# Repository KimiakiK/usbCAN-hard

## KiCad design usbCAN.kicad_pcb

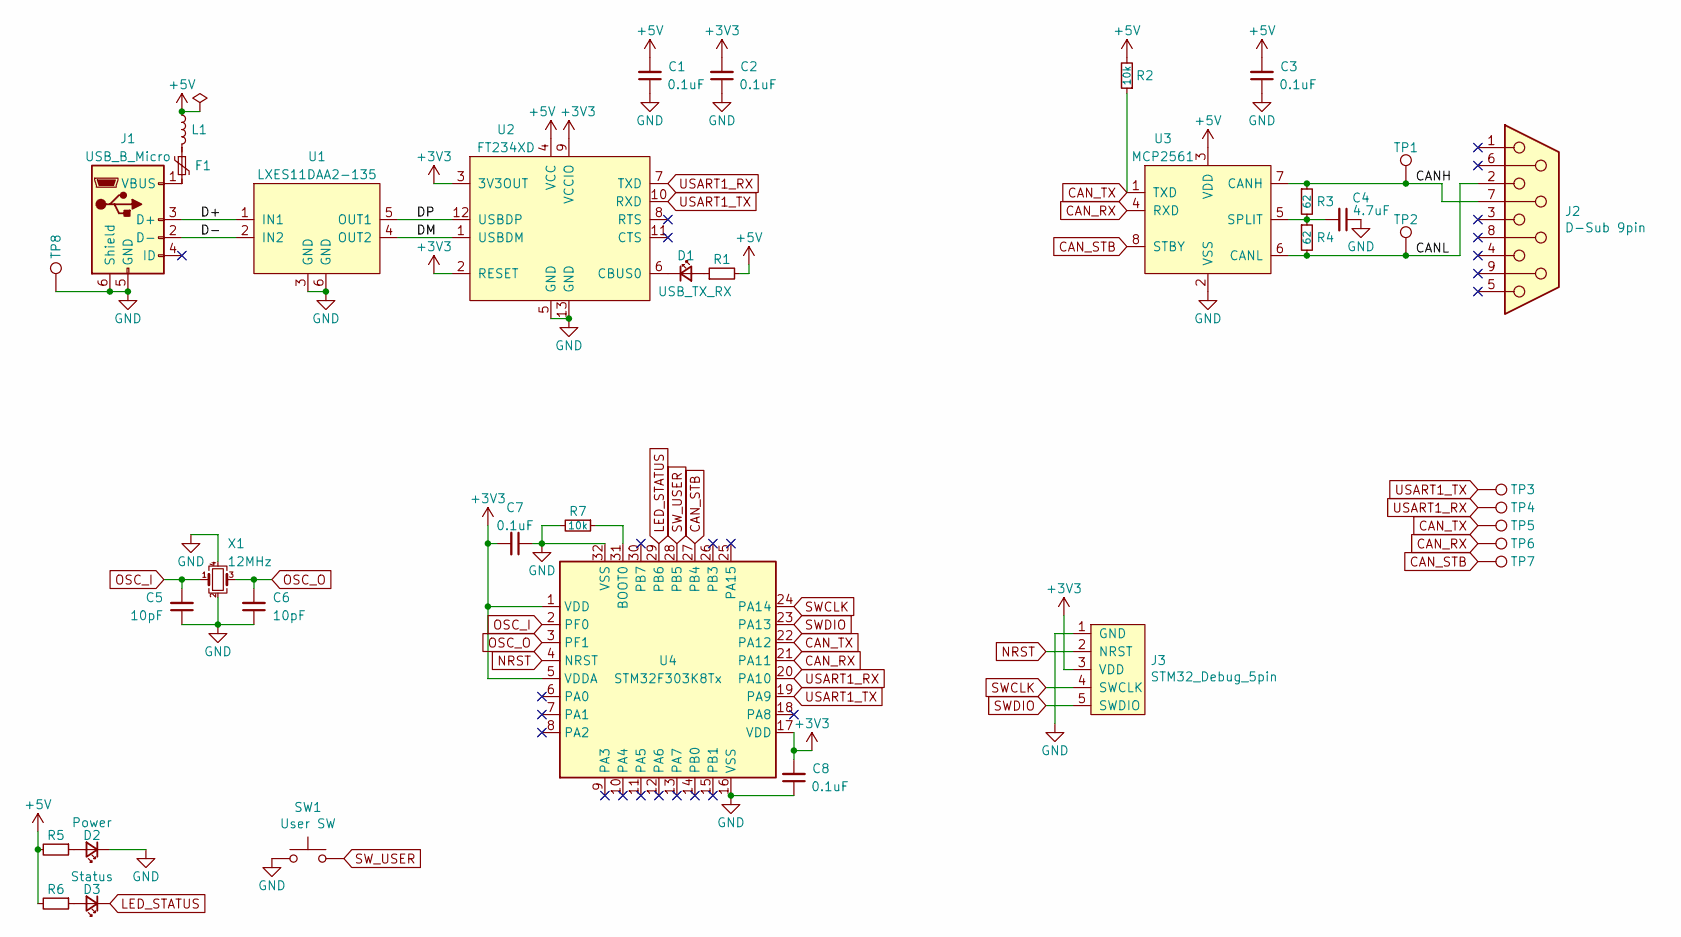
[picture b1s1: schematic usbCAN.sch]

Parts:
C1, C2, C3, C7, C8: 0.1uF; 1608Metric
C4: 4.7uF; 1608Metric
C5, C6: 10pF; 1005Metric
D1: USB_TX_RX; 1608Metric
D2: Power; 1608Metric
D3: Status; 1608Metric
F1: Polyfuse_Small; 1608Metric
J1: USB_B_Micro; ZX62-B-5PA
J2: D-Sub 9pin; DSUB-9_Male_Horizontal_P2.77x2.84mm_EdgePinOffset7.70mm_Hou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
J3: STM32_Debug_5pin
L1: L_Small; 1608Metric
R1, R5, R6: R_Small; 1608Metric
R2, R7: 10k; 1608Metric
R3, R4: 62; 1608Metric
SW1: User SW; SW_TVAF06
TP1, TP2, TP3, TP4, TP5, TP6, TP7, TP8: TestPoint; TestPoint_THTPad_2.0x2.0mm_Drill1.0mm
U1: LXES11DAA2-135; LXES11D
U2: FT234XD; DFN-12-1EP_3x3mm_P0.45mm_EP1.66x2.38mm
U3: MCP2561; DIP-8_W7.62mm_Socket
U4: STM32F303K8Tx; LQFP-32_7x7mm_P0.8mm_FusionPCB
X1: 12MHz; Crystal_SMD_3225-4Pin_3.2x2.5mm_HandSoldering

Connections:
+3V3: C2.2, C7.2, C8.2, J3.3 (VDD), U2.2 (RESET), U2.3 (3V3OUT), U2.9 (VCCIO), U4.1 (VDD), U4.5 (VDDA), U4.17 (VDD)
+5V: C1.2, C3.2, L1.1, R1.2, R2.2, R5.2, R6.2, U2.4 (VCC), U3.3 (VDD)
/CANH: J2.7, R3.1, TP1.1, U3.7 (CANH)
/CANL: J2.2, R4.2, TP2.1, U3.6 (CANL)
/D+: J1.3 (D+), U1.1 (IN1)
/D-: J1.2 (D-), U1.2 (IN2)
/DM: U1.4 (OUT2), U2.1 (USBDM)
/DP: U1.5 (OUT1), U2.12 (USBDP)
CAN_RX: TP6.1, U3.4 (RXD), U4.21 (PA11)
CAN_STB: TP7.1, U3.8 (STBY), U4.27 (PB4)
CAN_TX: R2.1, TP5.1, U3.1 (TXD), U4.22 (PA12)
GND: C1.1, C2.1, C3.1, C4.1, C5.1, C6.1, C7.1, C8.1, D2.1 (K), J1.5 (GND), J1.6 (Shield), J3.1 (GND), R7.2, SW1.1, TP8.1, U1.3 (GND), U1.6 (GND), U2.5 (GND), U2.13 (GND), U3.2 (VSS), U4.16 (VSS), U4.32 (VSS), X1.2, X1.4
LED_STATUS: D3.1 (K), U4.29 (PB6)
NRST: J3.2 (NRST), U4.4 (NRST)
unnamed: C4.2, R3.2, R4.1, U3.5 (SPLIT)
unnamed: D1.1 (K), U2.6 (CBUS0)
unnamed: D1.2 (A), R1.1
unnamed: D2.2 (A), R5.1
unnamed: D3.2 (A), R6.1
unnamed: F1.1, L1.2
unnamed: F1.2, J1.1 (VBUS)
unnamed: R7.1, U4.31 (BOOT0)
OSC_I: C5.2, U4.2 (PF0), X1.1
OSC_O: C6.2, U4.3 (PF1), X1.3
SWCLK: J3.4 (SWCLK), U4.24 (PA14)
SWDIO: J3.5 (SWDIO), U4.23 (PA13)
SW_USER: SW1.2, U4.28 (PB5)
USART1_RX: TP4.1, U2.7 (TXD), U4.20 (PA10)
USART1_TX: TP3.1, U2.10 (RXD), U4.19 (PA9)

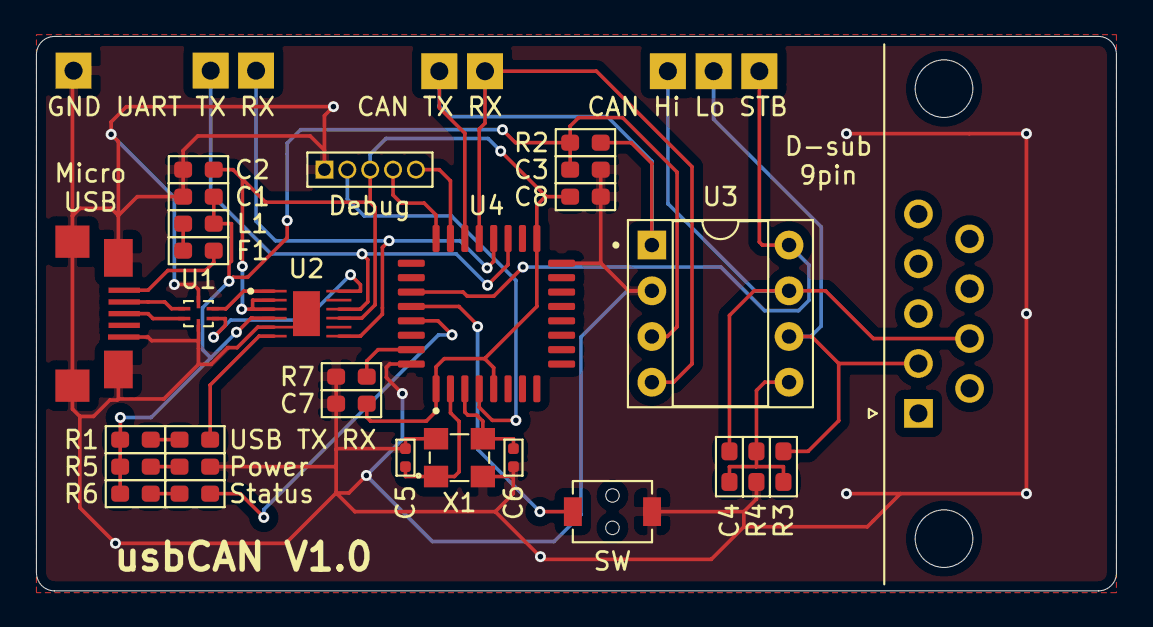
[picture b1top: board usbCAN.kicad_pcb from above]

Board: 2 copper layers, 60.0 x 30.8 mm, 37 parts (0 on the bottom side), 29 nets.

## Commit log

2021-04-11 基板 V1.0
